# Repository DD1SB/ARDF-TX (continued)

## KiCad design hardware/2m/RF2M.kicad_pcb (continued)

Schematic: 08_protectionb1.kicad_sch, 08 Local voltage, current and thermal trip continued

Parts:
C104, C804: 1n; C_0603_1608Metric_E3; MPN CC0603JRNPO9BN102
C801, C802, C803: 100n; C_0603_1608Metric_E3; MPN CC0603KRX7R8BB104
D801, D802: BAT54 fault AND; D_SOD-323_E3; MPN BAT54WS-7-F
R117: 1k; R_0603_1608Metric_E3; MPN RC0603FR-071KL
R118: 100k; R_0603_1608Metric_E3; MPN RC0603FR-07100KL; not fitted
R828: 5.11k; R_0603_1608Metric_E3; MPN RT0603BRD075K11L
R829: 4.02k; R_0603_1608Metric_E3; MPN RC0603FR-074K02L
R832, R833: 10k; R_0603_1608Metric_E3; MPN RC0603FR-0710KL
TP801: ISENSE; TestPoint_Pad_D1.0mm_E3; MPN PCB feature
TP802: POWER_FAULT_N; TestPoint_Pad_D1.0mm_E3; MPN PCB feature
U802, U803: LM339BDR; SOIC-14_3.9x8.7mm_P1.27mm_E3; MPN LM339BDR

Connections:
DRV_OV_REF: U802.9 (+); also elsewhere on the board
DRV_S: U802.8 (-); also elsewhere on the board
GND: C104.2, C801.2, C802.2, C803.2, C804.2, R118.2, R829.2, U802.12 (V-), U803.12 (V-); also elsewhere on the board
HARD_OK_N: D802.1 (K), R833.1, U802.13, U802.14, U803.1, U803.2, U803.13, U803.14; also elsewhere on the board
ISENSE: R828.1, TP801.1; also elsewhere on the board
ISENSE_F: C804.1, R828.2, R829.1, U803.4 (-)
OV_REF: U802.7 (+); also elsewhere on the board
PACK_OK_N: D801.1 (K), R832.1, U802.1, U802.2; also elsewhere on the board
PA_RAIL_ADC: C104.1, R117.2, R118.1; also elsewhere on the board
POWER_FAULT_N: D801.2 (A), D802.2 (A), TP802.1; also elsewhere on the board
REG_OV_REF: U802.11 (+); also elsewhere on the board
TEMP_HIGH: U803.11 (+); also elsewhere on the board
TEMP_LOW: U803.6 (-); also elsewhere on the board
TEMP_S: U803.7 (+), U803.10 (-); also elsewhere on the board
UV_REF: U802.4 (-); also elsewhere on the board
V3V3: C801.1, C802.1, C803.1, R832.2, R833.2, U802.3 (V+), U803.3 (V+); also elsewhere on the board
VBAT_S: U802.5 (+), U802.6 (-); also elsewhere on the board
VPA_OV_REF: U803.9 (+); also elsewhere on the board
VPA_S: U803.8 (-); also elsewhere on the board
VREF1V0: U803.5 (+); also elsewhere on the board
VREG_S: R117.1, U802.10 (-); also elsewhere on the board

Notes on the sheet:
08 Local voltage, current and thermal trip continued
M5B-E6R2 / integrated evaluation PCB / NOT RELEASED / hardware tests NOT_RUN
M5B-E6R2: REVIEW / ALL hardware measurements NOT RUN / no ordering or manufacture.

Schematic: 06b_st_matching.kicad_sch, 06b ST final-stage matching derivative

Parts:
C631, C633: 22p; C_0603_1608Metric_E3; MPN GRM1885C1H220JA01D
C632, C634, C639: 330p; C_0603_1608Metric_E3; MPN GRM1885C1H331JA01D
C635: 1u; C_0603_1608Metric_E3; MPN GRM188R71E105KA12D
C636: 33p; C_0603_1608Metric_E3; MPN GRM1885C1H330JA01D
C637: 100p; C_0603_1608Metric_E3; MPN GRM1885C1H101JA01D
C638: 39p; C_0603_1608Metric_E3; MPN GRM1885C1H390JA01D
L634: 47n; Coilcraft_0603HC_Doc218; MPN 0603HC-47NXJRW
L635: 33n; Coilcraft_1812SMS_Doc184; MPN 1812SMS-33NJLC
L638: 18.5n; Coilcraft_A05T_Doc107; MPN A05TJLC
TL603: 50R 6.1129mm; TL50_E3_6p1129mm; MPN PCB microstrip feature
TL604: 50R 6.4956mm; TL50_E3_6p4956mm; MPN PCB microstrip feature
TL605: 50R 5.691mm; TL50_E3_5p691mm; MPN PCB microstrip feature
TL606: 50R 2.1587mm; TL50_E3_2p1587mm; MPN PCB microstrip feature
TL607: 50R 10.7933mm; TL50_E3_10p7933mm; MPN PCB microstrip feature
TL608: 50R 12.167mm; TL50_E3_12p167mm; MPN PCB microstrip feature
TL609: 50R 1.9624mm; TL50_E3_1p9624mm; MPN PCB microstrip feature

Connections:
GND: C631.2, C633.2, C634.2, C635.2, C636.2, C637.2, C638.2; also elsewhere on the board
MMIC_AC: TL603.1 (IN); also elsewhere on the board
PA_DRAIN: L635.2, TL606.1 (IN); also elsewhere on the board
PA_GATE: TL605.2 (OUT); also elsewhere on the board
ST_DC_BLOCK: C639.2, TL609.1 (IN)
ST_IS_A: C631.1, C632.1, TL603.2 (OUT)
ST_IS_B: C632.2, TL604.1 (IN)
ST_IS_C: C633.1, L634.1, TL604.2 (OUT)
ST_IS_D: L634.2, TL605.1 (IN)
ST_LPF_IN: TL609.2 (OUT); also elsewhere on the board
ST_O_A: C636.1, TL606.2 (OUT), TL607.1 (IN)
ST_O_B: C637.1, L638.1, TL607.2 (OUT)
ST_O_C: C638.1, L638.2, TL608.1 (IN)
ST_O_D: C639.1, TL608.2 (OUT)
VMOD: C635.1; also elsewhere on the board
VPA: C634.1, L635.1; also elsewhere on the board

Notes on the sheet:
06b ST final-stage matching derivative
ST DocID17343 Rev1 Figs16/17/14. Traced topology; changed MMIC drive and supplyAM remain UNQUALIFIED. TLine symbols are PCB microstrip lengths, NOT purchased components or zero-length wire. No hardware measurements exist.
Input matching: original interstage source was PD84001 drain, not a50ohm MMIC. No claim of unchanged match or sufficient gain. Output matching/LPF retained. L63533n drain feed is a disclosed substitution for the contradictory35.5n/22n ST BOM entry. Use one integrated end-to-end commissioning proced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
M5B-E6R2: REVIEW / ALL hardware measurements NOT RUN / no ordering or manufacture.

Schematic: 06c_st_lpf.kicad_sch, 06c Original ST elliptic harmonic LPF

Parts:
C641: 3.3p; C_0603_1608Metric_E3; MPN GRM1885C1H3R3CA01D
C642: 18p; C_0603_1608Metric_E3; MPN GRM1885C1H180JA01D
C643: 12p; C_0603_1608Metric_E3; MPN GRM1885C1H120JA01D
C644, C646: 22p; C_0603_1608Metric_E3; MPN GRM1885C1H220JA01D
C645: 27p; C_0603_1608Metric_E3; MPN GRM1885C1H270JA01D
C647: 15p; C_0603_1608Metric_E3; MPN GRM1885C1H150JA01D
L641: 39n; Coilcraft_1008CS_Doc101; MPN 1008CS-390XJLC
L642: 22n; Coilcraft_1008CS_Doc101; MPN 1008CS-220XJLC
L643: 27n; Coilcraft_1008CS_Doc101; MPN 1008CS-270XJLC

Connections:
GND: C644.2, C645.2, C646.2, C647.2; also elsewhere on the board
NORMAL_RF: C643.2, C647.1, L643.2; also elsewhere on the board
ST_F1: C641.2, C642.1, C645.1, L641.2, L642.1
ST_F2: C642.2, C643.1, C646.1, L642.2, L643.1
ST_LPF_IN: C641.1, C644.1, L641.1; also elsewhere on the board

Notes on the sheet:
06c Original ST elliptic harmonic LPF
ST DocID17343 Rev1 Figs16/17/14. Traced topology; changed MMIC drive and supplyAM remain UNQUALIFIED. TLine symbols are PCB microstrip lengths, NOT purchased components or zero-length wire. No hardware measurements exist.
Input matching: original interstage source was PD84001 drain, not a50ohm MMIC. No claim of unchanged match or sufficient gain. Output matching/LPF retained. L63533n drain feed is a disclosed substitution for the contradictory35.5n/22n ST BOM entry. Use one integrated end-to-end commissioning proced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
M5B-E6R2: REVIEW / ALL hardware measurements NOT RUN / no ordering or manufacture.

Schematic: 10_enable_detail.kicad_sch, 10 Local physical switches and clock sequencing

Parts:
C931, C940, C941: 100n; C_0603_1608Metric_E3; MPN CC0603KRX7R8BB104
D930: BAT54WS; D_SOD-323_E3; MPN BAT54WS-7-F
R930: 10k; R_0603_1608Metric_E3; MPN RC0603FR-0710KL
R931: 330; R_0603_1608Metric_E3; MPN RC0603FR-07330RL
R932, R940: 100k; R_0603_1608Metric_E3; MPN RC0603FR-07100KL
TP940: Captured profile; TestPoint_Pad_D1.0mm_E3; MPN PCB feature
U205: 74HC21D,653; SOIC-14_3.9x8.7mm_P1.27mm_E3; MPN 74HC21D,653
U206: 74HC11D,653; SOIC-14_3.9x8.7mm_P1.27mm_E3; MPN 74HC11D,653
U305: TPS22810DBVR; SOT-23-6_E3; MPN TPS22810DBVR
U601: SN74LVC1G125DBVR; SOT-23-5_E3; MPN SN74LVC1G125DBVR

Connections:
ARM: U205.5; also elsewhere on the board
ARM_DELAY: U205.2; also elsewhere on the board
CLEAR_A: U205.9, U206.5, U206.13; also elsewhere on the board
CLK_NORMAL: U601.2 (A); also elsewhere on the board
CLOCK_OFF: U601.1 (OE_N); also elsewhere on the board
CLR_N: U205.8; also elsewhere on the board
CONV_EN: U206.8; also elsewhere on the board
DRIVER_ON: U305.3 (EN); also elsewhere on the board
GND: C931.2, C940.2, C941.2, R932.2, R940.2, U205.7 (GND), U206.7 (GND), U305.2 (GND), U601.3 (GND); also elsewhere on the board
NORMAL_CLOCK_BUF: U601.4 (Y); also elsewhere on the board
NORMAL_FAST_OFF: D930.1 (K), R931.1
NORMAL_PERMIT: R930.1, R931.2, R940.1, U206.12; also elsewhere on the board
NORMAL_Q: U206.2; also elsewhere on the board
NORMAL_RC: C931.1, D930.2 (A), R930.2, R932.1; also elsewhere on the board
PATH_Q: U206.4; also elsewhere on the board
PA_PREPARE: U206.9; also elsewhere on the board
PROFILE_Q: TP940.1; also elsewhere on the board
RUN_HEALTH: U205.10; also elsewhere on the board
SLOT: U205.4; also elsewhere on the board
SRC_ON: U206.10; also elsewhere on the board
TRAIN_PERMIT: U206.6; also elsewhere on the board
TX_OK: U205.6, U206.1, U206.3
V3V3: C941.1, U205.12, U205.13, U205.14 (VCC), U206.11, U206.14 (VCC), U601.5 (VCC); also elsewhere on the board
VALID_ARM: U205.1; also elsewhere on the board
VDRV_FILTER: C940.1, U305.1 (VIN); also elsewhere on the board
VDRV_RF: U305.5 (QOD), U305.6 (VOUT); also elsewhere on the board

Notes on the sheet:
10 Local physical switches and clock sequencing
M5B-E6R2 / integrated evaluation PCB / NOT RELEASED / hardware tests NOT_RUN
M5B-E6R2: REVIEW / ALL hardware measurements NOT RUN / no ordering or manufacture.

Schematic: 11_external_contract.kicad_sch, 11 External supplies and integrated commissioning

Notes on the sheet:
11 External supplies and integrated commissioning
M5B-E6R2 / integrated evaluation PCB / NOT RELEASED / hardware tests NOT_RUN
M5B-E6R2: REVIEW / ALL hardware measurements NOT RUN / no ordering or manufacture.

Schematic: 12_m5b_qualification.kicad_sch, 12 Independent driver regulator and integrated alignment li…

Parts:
C950, C951: 4.7u; C_0805_2012Metric_E3; MPN GRM21BR71E475KA73L
C960: 22u; C_1210_3225Metric_E3; MPN GRM32ER71V226KE15L
C961: 22u; C_1210_3225Metric_E3; MPN GRM32ER71V226KE15L; not fitted
R650: 0; R_0603_1608Metric_E3; MPN RC0603JR-070RL
R651: 49.9; R_1206_3216Metric_E3; MPN RC1206FR-0749R9L; not fitted
R950: 58.2k; R_0603_1608Metric_E3; MPN RT0603BRD0758K2L
R951: 10k; R_0603_1608Metric_E3; MPN RT0603BRD0710KL
R952: 0; R_1206_3216Metric_E3; MPN RC1206JR-070RL
TP950: DRV pre5.456V; TestPoint_Pad_D1.0mm_E3; MPN PCB feature
TP951: MMIC isolated5V; TestPoint_Pad_D1.0mm_E3; MPN PCB feature
U950: TLV76701DRVR; WSON-6-1EP_2x2mm_P0.65mm_EP1x1.6mm_E3; MPN TLV76701DRVR

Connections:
CONV_EN: U950.4 (EN); also elsewhere on the board
DRV_PRE_FB: R950.2, R951.1, U950.2 (FB)
GND: C950.2, C951.2, C960.2, C961.2, R651.2, R951.2, U950.3 (GND), U950.5 (GND), U950.7 (EP_GND); also elsewhere on the board
MMIC_AC: R650.2; also elsewhere on the board
MMIC_COUPLED: R650.1, R651.1; also elsewhere on the board
VDRV_LDO_IN: C950.1, U950.6 (IN); also elsewhere on the board
VDRV_MMIC: R952.2, TP951.1; also elsewhere on the board
VDRV_PREREG: C951.1, R950.1, TP950.1, U950.1 (OUT); also elsewhere on the board
VDRV_RF: R952.1; also elsewhere on the board
VIN_CONV: C960.1, C961.1; also elsewhere on the board

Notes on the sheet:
12 Independent driver regulator and integrated alignment links
Pre-regulation5.456V then existing5V LDO. Rated18V switch. No20us RC assumption is claimed as protection proof. Fit driver link only after power-only qualification. RF link and optional50ohm load permit alignment on THIS board.
M5B-E6R2: REVIEW / ALL hardware measurements NOT RUN / no ordering or manufacture.

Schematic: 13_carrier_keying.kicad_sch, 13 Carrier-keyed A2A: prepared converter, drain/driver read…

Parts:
C970, C971, C972, C973: 100n; C_0603_1608Metric_E3; MPN GRM188R71H104KA93D
R970: 0.05; R_2512_6332Metric_E3; MPN WSL2512R0500FEA
R971, R975, R979, R980, R981, R982, R983, R984, R986: 100k; R_0603_1608Metric_E3; MPN RT0603BRD07100KL
R972, R976: 33k; R_0603_1608Metric_E3; MPN RT0603BRD0733KL
R973: 330k; R_0603_1608Metric_E3; MPN RT0603BRD07330KL
R974: 2.49k; R_0603_1608Metric_E3; MPN RT0603BRD072K49L
R977: 19.1k; R_0603_1608Metric_E3; MPN RT0603BRD0719K1L
R978, R985: 10k; R_0603_1608Metric_E3; MPN RT0603BRD0710KL
TP970: Pass collector before current shunt; TestPoint_Pad_D1.0mm_E3; MPN PCB feature
TP971: Regulated current shunt upstream; TestPoint_Pad_D1.0mm_E3; MPN PCB feature
TP972: RF inhibit; TestPoint_Pad_D1.0mm_E3; MPN PCB feature
TP973: MMIC enable; TestPoint_Pad_D1.0mm_E3; MPN PCB feature
TP974: Modulator clamp; TestPoint_Pad_D1.0mm_E3; MPN PCB feature
TP975: PA readiness; TestPoint_Pad_D1.0mm_E3; MPN PCB feature
TP976: Driver readiness; TestPoint_Pad_D1.0mm_E3; MPN PCB feature
U970: TLV7032DGKR; TLV7032_DGK_E6R2; MPN TLV7032DGKR
U971: SN74LVC1G00DBVR; LVC1G00_DBV_E6R2; MPN SN74LVC1G00DBVR
U972: SN74LVC2G32DCTR; LVC2G32_DCT_E6R2; MPN SN74LVC2G32DCTR
U973: SN74LVC1G04DBVR; LVC1G04_DBV_E6R2; MPN SN74LVC1G04DBVR

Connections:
CLOCK_OFF: R981.1, TP972.1, U972.3 (2Y); also elsewhere on the board
DRIVER_ON: R982.1, TP973.1, U973.4 (Y); also elsewhere on the board
DRV_READY: R980.1, TP976.1, U970.7 (OUTB), U971.2 (B)
DRV_READY_REF: R977.2, R978.1, U970.6 (INB-)
DRV_READY_S: R975.2, R976.1, U970.5 (INB+)
GND: C970.2, C971.2, C972.2, C973.2, R972.2, R974.2, R976.2, R978.2, R979.2, R980.2, R982.2, R986.2, U970.4 (GND), U971.3 (GND), U972.4 (GND), U973.3 (GND); also elsewhere on the board
KEY_N: U972.2 (1B); also elsewhere on the board
LOCAL_MOD_OFF: R984.1, TP974.1, U972.5 (2A), U972.7 (1Y), U973.2 (A); also elsewhere on the board
MOD_COMMAND_OFF_BASE: R985.2, R986.1; also elsewhere on the board
NORMAL_OFF: R985.1, U972.1 (1A); also elsewhere on the board
RF_NOT_READY: R983.1, U971.4 (Y), U972.6 (2B)
V3V3: C970.1, C971.1, C972.1, C973.1, R973.1, R977.1, R981.2, R983.2, R984.2, U970.8 (VCC), U971.5 (VCC), U972.8 (VCC), U973.5 (VCC); also elsewhere on the board
VDRV_MMIC: R975.1; also elsewhere on the board
VPA: R970.2, R971.1; also elsewhere on the board
VPA_PRE: R970.1, TP970.1; also elsewhere on the board
VPA_READY: R979.1, TP975.1, U970.1 (OUTA), U971.1 (A)
VPA_READY_REF: R973.2, R974.1, U970.2 (INA-)
VPA_READY_S: R971.2, R972.1, U970.3 (INA+)
VREG_SWITCH: TP971.1; also elsewhere on the board

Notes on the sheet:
13 Carrier-keyed A2A: prepared converter, drain/driver readiness and probes
Architecture C: LOCAL_MOD_OFF=NORMAL_OFF OR KEY_N; DRIVER_ON=NOT LOCAL_MOD_OFF. CLOCK_OFF=LOCAL_MOD_OFF OR NOT(VPA_READY AND DRV_READY). Native safety delay/fastkill remain in series. AF_PWM must provide shaped sine envelope; KEY gives preparation lead. No converter re-start per Morse element. Exis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
M5B-E6R2: REVIEW / ALL hardware measurements NOT RUN / no ordering or manufacture.
Carrier keying

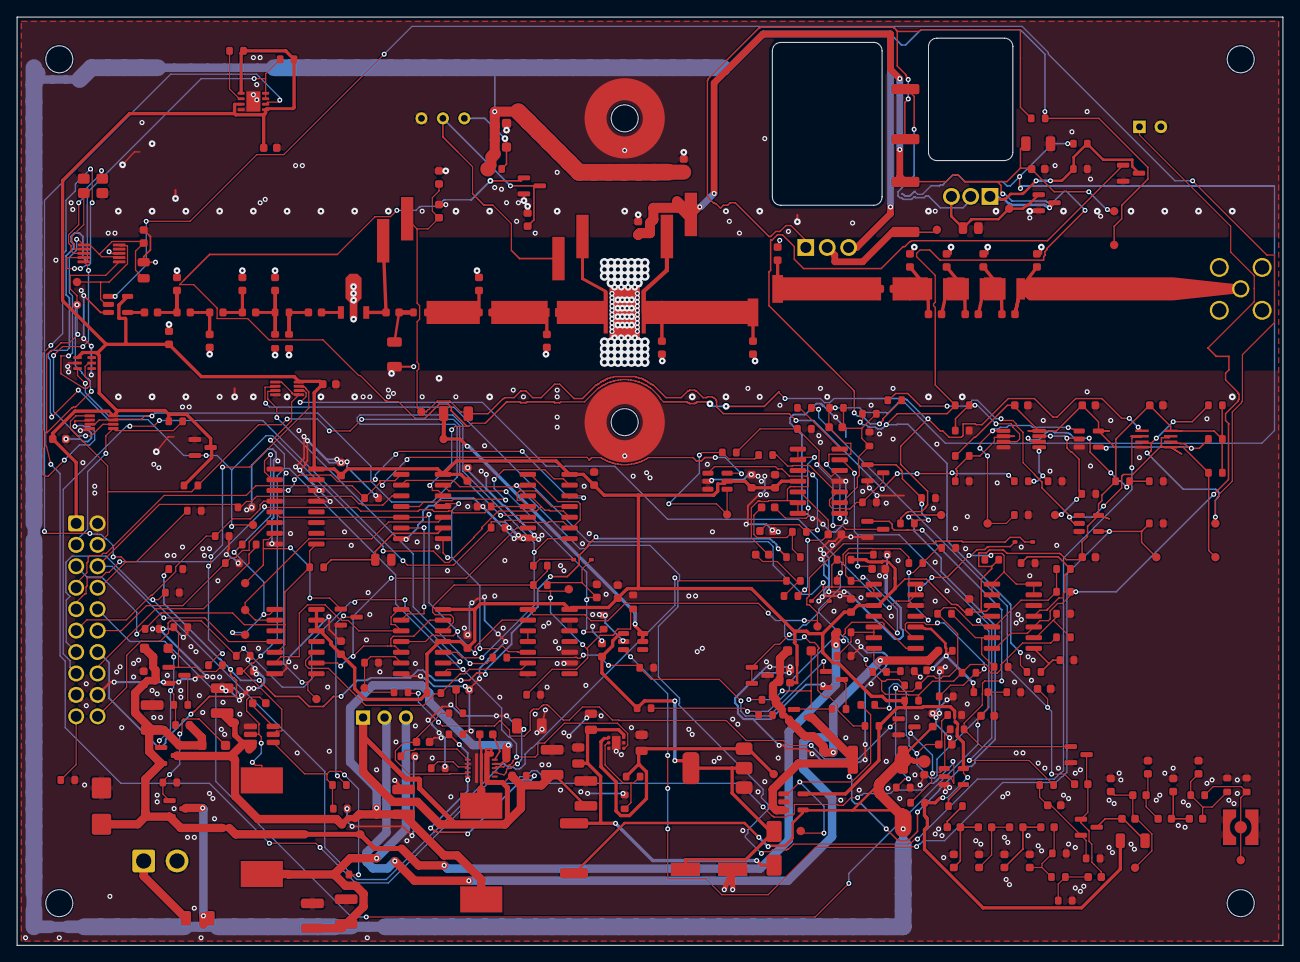
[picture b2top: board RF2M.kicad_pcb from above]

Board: 2 copper layers, 150.0 x 110.0 mm, 358 parts (0 on the bottom side), 181 nets.

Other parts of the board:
H1, H2, H3, H4, H5, H6: MountingHole_3.2mm_M3; MountingHole_3.2mm_M3_E3

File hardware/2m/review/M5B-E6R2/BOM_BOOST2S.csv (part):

variant,fleet,ref,value,MPN,footprint,quantity_board,order_pooled,MOQ,multiple,unit_net_EUR,allocated_net_EUR,evidence,supplier,availability,source
BOOST2S,7,J101,Controller 20 pin,61202021621,ARDF_2M:WR_BHD_61202021621,1,7,1,1,0.65,0.65,ESTIMATE,Wurth authorized distributor,Not independently basket-confirmed,https://www.we-online.com/components/products/datasheet/6120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
BOOST2S,7,R101,18.2k,RC0603FR-0718K2L,ARDF_2M:R_0603_1608Metric_E3,1,7,1,1,0.02,0.02,ESTIMATE,OPEN,Not independently basket-confirmed,https://www.yageo.com/en/ProductCategory/Resistors
BOOST2S,7,R102,4.7k,RC0603FR-074K7L,ARDF_2M:R_0603_1608Metric_E3,1,56,1,1,0.02,0.02,ESTIMATE,OPEN,Not independently basket-confirmed,https://www.yageo.com/en/ProductCategory/Resistors
BOOST2S,7,R103,4.7k,RC0603FR-074K7L,ARDF_2M:R_0603_1608Metric_E3,1,56,1,1,0.02,0.02,ESTIMATE,OPEN,Not independently basket-confirmed,https://www.yageo.com/en/ProductCategory/Resistors
BOOST2S,7,R104,100k,RC0603FR-07100KL,ARDF_2M:R_0603_1608Metric_E3,1,140,1,1,0.02,0.02,ESTIMATE,OPEN,Not independently basket-confirmed,https://www.yageo.com/en/ProductCategory/Resistors
BOOST2S,7,R105,100k,RC0603FR-07100KL,ARDF_2M:R_0603_1608Metric_E3,1,140,1,1,0.02,0.02,ESTIMATE,OPEN,Not independently basket-confirmed,https://www.yageo.com/en/ProductCategory/Resistors
BOOST2S,7,R106,100k,RC0603FR-07100KL,ARDF_2M:R_0603_1608Metric_E3,1,140,1,1,0.02,0.02,ESTIMATE,OPEN,Not independently basket-confirmed,https://www.yageo.com/en/ProductCategory/Resistors
BOOST2S,7,R107,100k,RC0603FR-07100KL,ARDF_2M:R_0603_1608Metric_E3,1,140,1,1,0.02,0.02,ESTIMATE,OPEN,Not independently basket-confirmed,https://www.yageo.com/en/ProductCategory/Resistors
BOOST2S,7,R108,100k,RC0603FR-07100KL,ARDF_2M:R_0603_1608Metric_E3,1,140,1,1,0.02,0.02,ESTIMATE,OPEN,Not independently basket-confirmed,https://www.yageo.com/en/ProductCategory/Resistors
BOOST2S,7,R109,100k,RC0603FR-07100KL,ARDF_2M:R_0603_1608Metric_E3,1,140,1,1,0.02,0.02,ESTIMATE,OPEN,Not independently basket-confirmed,https://www.yageo.com/en/ProductCategory/Resistors
BOOST2S,7,R110,100k,RC0603FR-07100KL,ARDF_2M:R_0603_1608Metric_E3,1,140,1,1,0.02,0.02,ESTIMATE,OPEN,Not independently basket-confirmed,https://www.yageo.com/en/ProductCategory/Resistors
BOOST2S,7,R111,100k,RC0603FR-07100KL,ARDF_2M:R_0603_1608Metric_E3,1,140,1,1,0.02,0.02,ESTIMATE,OPEN,Not independently basket-confirmed,https://www.yageo.com/en/ProductCategory/Resistors
BOOST2S,7,R112,100k,RC0603FR-07100KL,ARDF_2M:R_0603_1608Metric_E3,1,140,1,1,0.02,0.02,ESTIMATE,OPEN,Not independently basket-confirmed,https://www.yageo.com/en/ProductCategory/Resistors
BOOST2S,7,R115,100k,RC0603FR-07100KL,ARDF_2M:R_0603_1608Metric_E3,1,140,1,1,0.02,0.02,ESTIMATE,OPEN,Not independently basket-confirmed,https://www.yageo.com/en/ProductCategory/Resistors
BOOST2S,7,R116,100k,RC0603FR-07100KL,ARDF_2M:R_0603_1608Metric_E3,1,140,1,1,0.02,0.02,ESTIMATE,OPEN,Not independently basket-confirmed,https://www.yageo.com/en/ProductCategory/Resistors
BOOST2S,7,U101,TPS22919DCKR,TPS22919DCKR,ARDF_2M:SOT-363_SC-70-6_E3,1,7,1,1,0.25,0.25,ESTIMATE,OPEN,Not independently basket-confirmed,https://www.ti.com/lit/ds/symlink/tps22919.pdf
BOOST2S,7,U102,SN74LVC2G66DCUR,SN74LVC2G66DCUR,ARDF_2M:VSSOP-8_2.3x2mm_P0.5mm_E3,1,7,1,1,0.33,0.33,ESTIMATE,OPEN,Not independently basket-confirmed,https://www.ti.com/lit/ds/symlink/sn74lvc2g66.pdf
BOOST2S,7,U103,Si5351A-B-GT,Si5351A-B-GT,ARDF_2M:MSOP-10_3x3mm_P0.5mm_E3,1,7,1,1,1.35,1.35,ESTIMATE,OPEN,Not independently basket-confirmed,https://www.skyworksinc.com/-/media/SkyWorks/SL/documents/pu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
BOOST2S,7,Y101,25MHz CL10p 10/10ppm,ABM8-25.000MHZ-10-B1U-T,ARDF_2M:Crystal_SMD_3225-4Pin_3.2x2.5mm_E3,1,7,1,1,0.35,0.35,ESTIMATE,OPEN,Not independently basket-confirmed,
BOOST2S,7,C101,100n,CC0603KRX7R8BB104,ARDF_2M:C_0603_1608Metric_E3,1,175,1,1,0.045,0.045,ESTIMATE,OPEN,Not independently basket-confirmed,
BOOST2S,7,C102,100n,CC0603KRX7R8BB104,ARDF_2M:C_0603_1608Metric_E3,1,175,1,1,0.045,0.045,ESTIMATE,OPEN,Not independently basket-confirmed,
BOOST2S,7,C103,1u,CC0805KKX7R9BB105,ARDF_2M:C_0805_2012Metric_E3,1,21,1,1,0.045,0.045,ESTIMATE,OPEN,Not independently basket-confirmed,
BOOST2S,7,U201,TPS3431SDRBR,TPS3431SDRBR,ARDF_2M:VSON-8-1EP_3x3mm_P0.65mm_EP1.65x2.4mm_E3,1,7,1,1,0.85,0.85,ESTIMATE,OPEN,Not independently basket-confirmed,https://www.ti.com/lit/ds/symlink/tps3431.pdf
BOOST2S,7,R201,10k,RC0603FR-0710KL,ARDF_2M:R_0603_1608Metric_E3,1,196,1,1,0.02,0.02,ESTIMATE,OPEN,Not independently basket-confirmed,https://www.yageo.com/en/ProductCategory/Resistors
BOOST2S,7,R202,10k,RC0603FR-0710KL,ARDF_2M:R_0603_1608Metric_E3,1,196,1,1,0.02,0.02,ESTIMATE,OPEN,Not independently basket-confirmed,https://www.yageo.com/en/ProductCategory/Resistors
BOOST2S,7,C201,100n,CC0603KRX7R8BB104,ARDF_2M:C_0603_1608Metric_E3,1,175,1,1,0.045,0.045,ESTIMATE,OPEN,Not independently basket-confirmed,
BOOST2S,7,U208,TLV803EA29DBZR,TLV803EA29DBZR,ARDF_2M:SOT-23_E3,1,7,1,1,0.19,0.19,ESTIMATE,OPEN,Not independently basket-confirmed,https://www.ti.com/lit/ds/symlink/tlv803e.pdf
BOOST2S,7,U202,"74HC174D,653","74HC174D,653",ARDF_2M:SOIC-16_3.9x9.9mm_P1.27mm_E3,1,7,1,1,0.48,0.48,ESTIMATE,OPEN,Not independently basket-confirmed,https://assets.nexperia.com/documents/data-sheet/74HC_HCT174.pdf
BOOST2S,7,U203,"74HC14D,653","74HC14D,653",ARDF_2M:SOIC-14_3.9x8.7mm_P1.27mm_E3,1,7,1,1,0.28,0.28,ESTIMATE,OPEN,Not independently basket-confirmed,https://assets.nexperia.com/documents/data-sheet/74HC_HCT14.pdf
BOOST2S,7,U204,"74HC11D,653","74HC11D,653",ARDF_2M:SOIC-14_3.9x8.7mm_P1.27mm_E3,1,14,1,1,0.28,0.28,ESTIMATE,OPEN,Not independently basket-confirmed,https://assets.nexperia.com/documents/data-sheet/74HC_HCT11.pdf
BOOST2S,7,U207,"74HC32D,653","74HC32D,653",ARDF_2M:SOIC-14_3.9x8.7mm_P1.27mm_E3,1,7,1,1,0.28,0.28,ESTIMATE,OPEN,Not independently basket-confirmed,https://assets.nexperia.com/documents/data-sheet/74HC_HCT32.pdf
BOOST2S,7,R203,10k,RC0603FR-0710KL,ARDF_2M:R_0603_1608Metric_E3,1,196,1,1,0.02,0.02,ESTIMATE,OPEN,Not independently basket-confirmed,https://www.yageo.com/en/ProductCategory/Resistors
BOOST2S,7,C202,1u,CC0805KKX7R9BB105,ARDF_2M:C_0805_2012Metric_E3,1,21,1,1,0.045,0.045,ESTIMATE,OPEN,Not independently basket-confirmed,
BOOST2S,7,R204,100k,RC0603FR-07100KL,ARDF_2M:R_0603_1608Metric_E3,1,140,1,1,0.02,0.02,ESTIMATE,OPEN,Not independently basket-confirmed,https://www.yageo.com/en/ProductCategory/Resistors
BOOST2S,7,R205,100k,RC0603FR-07100KL,ARDF_2M:R_0603_1608Metric_E3,1,140,1,1,0.02,0.02,ESTIMATE,OPEN,Not independently basket-confirmed,https://www.yageo.com/en/ProductCategory/Resistors
BOOST2S,7,C203,100n,CC0603KRX7R8BB104,ARDF_2M:C_0603_1608Metric_E3,1,175,1,1,0.045,0.045,ESTIMATE,OPEN,Not independently basket-confirmed,
BOOST2S,7,C204,100n,CC0603KRX7R8BB104,ARDF_2M:C_0603_1608Metric_E3,1,175,1,1,0.045,0.045,ESTIMATE,OPEN,Not independently basket-confirmed,
BOOST2S,7,C205,100n,CC0603KRX7R8BB104,ARDF_2M:C_0603_1608Metric_E3,1,175,1,1,0.045,0.045,ESTIMATE,OPEN,Not independently basket-confirmed,
BOOST2S,7,C206,100n,CC0603KRX7R8BB104,ARDF_2M:C_0603_1608Metric_E3,1,175,1,1,0.045,0.045,ESTIMATE,OPEN,Not independently basket-confirmed,
BOOST2S,7,C207,100n,CC0603KRX7R8BB104,ARDF_2M:C_0603_1608Metric_E3,1,175,1,1,0.045,0.045,ESTIMATE,OPEN,Not independently basket-confirmed,
BOOST2S,7,C208,100n,CC0603KRX7R8BB104,ARDF_2M:C_0603_1608Metric_E3,1,175,1,1,0.045,0.045,ESTIMATE,OPEN,Not independently basket-confirmed,
BOOST2S,7,R206,1k,RC0603FR-071KL,ARDF_2M:R_0603_1608Metric_E3,1,70,1,1,0.02,0.02,ESTIMATE,OPEN,Not independently basket-confirmed,https://www.yageo.com/en/ProductCategory/Resistors
BOOST2S,7,J301,Protected pack JST VH,B2P-VH(LF)(SN),ARDF_2M:JST_VH_B2P-VH_1x02_P3.96mm_Vertical_E3,1,7,1,1,0.35,0.35,ESTIMATE,JST authorized distributor,Not independently basket-confirmed,https://www.jst.com/wp-content/uploads/2025/06/eVH.pdf
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
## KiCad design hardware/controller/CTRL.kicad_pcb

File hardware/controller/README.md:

# ARDF-TX universal controller — M6-L2 candidate

Active KiCad 10 sources are CTRL.kicad_pro, CTRL.kicad_sch, its referenced sheets and CTRL.kicad_pcb, with local ARDF_CTL libraries. M6-L2 selects ESP32-S3-WROOM-1U-N4 (4 MB flash, no PSRAM), adds optional FoxPro2 compatibility and an optional TCA9534APWR eight-line GPIO interface. See the [review package](review/M6-L2/README.md), [decision](../../docs/M6_L2_REVIEW_DECISION.md) and [reproduction commands](review/M6-L2/REPRODUCE.md).

[M6-L1](review/M6-L1/README.md) remains the previous independently reviewed baseline. Its NO_LORA, LORA_433 and LORA_868 options, module footprint and RF feed remain. RF80/RF2M sources and historical review packages are immutable. All existing GPIO functions, protected battery ID, USB/reset/RTC facilities, RF branch isolation, static controls and fail-off architecture are retained. PACK_ID_FRONTEND_REV2 calibration and the external 10k/22k identities remain mandatory.

The default build retains recovery UART routing and omits both new interfaces. FoxPro population replaces the recovery links with physically separate routing links; never fit both sets. The ESP32's 2.4 GHz antenna is separate from LoRa. Legacy FoxPro battery display is unavailable on both 2S and 4S. GPIO3/46 service links remain open; GPIO45 remains NC without breakout. Select one of the 48 explicit RF/LoRa/interface populations and use its assembly/placement files. An SX1262 response cannot identify its RF band; unknown LoRa disables LoRa TX while otherwise valid autonomous operation remains available.

Independent review and [fresh final reproduction](../../docs/M6_L2_FINAL_REPRODUCTION.md) support GO for five controlled bare evaluation boards. The verified revision is authorized for normal GitHub publication. All physical ESP32/USB/recovery, genuine FoxPro, antenna/coexistence, accessory, fault, power-sequencing and RF/thermal qualification is NOT_RUN. Host foundations are not complete contest firmware. No supplier upload, order, purchase, hardware energizing, acceptance tag or production release is authorized.

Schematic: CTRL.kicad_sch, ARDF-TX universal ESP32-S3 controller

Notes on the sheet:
M6-L1 UNIVERSAL CONTROLLER / ENGINEERING CANDIDATE ESP32-S3-WROOM-1-N4 / RV-3032-C7 / isolated RF80 + RF2M contracts No manufacturing or operational release. All physical tests NOT_RUN. LoRa optional433/868 nominal package/RF-feed audit M6-L1; trusted assembly configuration required. Physical tests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

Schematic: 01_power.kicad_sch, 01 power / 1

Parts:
C1, C6: 100n; C_0603_1608Metric_CTL; MPN CL10B104KB8NNNC
C2, C3: 4.7u 50V; C_1210_3225Metric_CTL; MPN GRM32ER71H475KA88L
C4, C5: 22u 10V; C_1206_3216Metric_CTL; MPN CL31A226KPHNNNE
D1: 100V 2A reverse block; D_SMA_CTL; MPN STPS2H100A
D2: 18V unidirectional TVS; D_SMB_CTL; MPN SMBJ18A
D3: USB low-drop OR; D_SMA_CTL; MPN STPS1L30A
D4: Low leakage battery OR; D_SMA_CTL; MPN S1M-E3/61T
D21: USB reverse-leak clamp 5.1V; D_SOD-123F_CTL; MPN BZT52H-B5V1,115
F1: 1A 63V fast; Fuse_Bourns_SF1206F; MPN SF-1206F100-2
J1: PACK / GND / ID; JST_XH_B3B_Standard; MPN B3B-XH-A(LF)(SN)
L1: 4.7uH 4.6Arms; L_Bourns_SRP5030T_CTL; MPN SRP5030T-4R7M
R1: 470k; R_0603_1608Metric_CTL; MPN RC0603FR-07470KL
R2: 47k; R_0603_1608Metric_CTL; MPN RC0603FR-0747KL
R3: 27k; R_0603_1608Metric_CTL; MPN RC0603FR-0727KL
U1: AP63203WU-7; TSOT-23-6_CTL; MPN AP63203WU-7

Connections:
BAT_DIV: R1.2, R2.1; also elsewhere on the board
BUCK_BST: C1.1, U1.6 (6_BST)
BUCK_SW: C1.2, L1.1, U1.5 (5_SW)
GND: C2.2, C3.2, C4.2, C5.2, C6.2, D2.2 (A), D21.2 (A), J1.2 (2_IO), R2.2, U1.4 (4_GND); also elsewhere on the board
PACK_FUSED: D1.2 (A), F1.2
PACK_ID_EXC: R3.1; also elsewhere on the board
PACK_ID_RAW: J1.3 (3_IO), R3.2; also elsewhere on the board
PACK_PROT: D1.1 (K), D2.1 (K), D4.2 (A), R1.1; also elsewhere on the board
PACK_RAW: F1.1, J1.1 (1_IO)
USB_LIMIT: D3.2 (A), D21.1 (K); also elsewhere on the board
V3V3: C4.1, C5.1, C6.1, L1.2, U1.1 (1_FB); also elsewhere on the board
VIN_SYS: C2.1, C3.1, D3.1 (K), D4.1 (K), U1.2 (2_EN), U1.3 (3_VIN); also elsewhere on the board

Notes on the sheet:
01 power / 1
M6-C1R1 candidate: REVIEW / ALL hardware measurements NOT RUN / no ordering or manufacture.

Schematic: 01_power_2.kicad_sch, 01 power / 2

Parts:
D22: BAS116 ID excitation isolation; SOT-23_CTL; MPN BAS116,235
D23: BAT54H negative ID clamp; D_SOD-123F_CTL; MPN BAT54H,115
Q1: MMBT3904; SOT-23_CTL; MPN MMBT3904LT1G
R4, R5, R19: 100k; R_0603_1608Metric_CTL; MPN RC0603FR-07100KL
R6, R7: 10k; R_0603_1608Metric_CTL; MPN RC0603FR-0710KL
R8: 180k; R_0603_1608Metric_CTL; MPN RC0603FR-07180KL
R9: 33k; R_0603_1608Metric_CTL; MPN RC0603FR-0733KL

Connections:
BATT_BASE: Q1.1 (1_B), R4.2, R5.1
GND: D23.2 (A), Q1.2 (2_E), R5.2, R7.2, R9.2, R19.2; also elsewhere on the board
PACK_ABSENT: Q1.3 (3_C), R6.2; also elsewhere on the board
PACK_ID_ADC: R19.1; also elsewhere on the board
PACK_ID_EXC: D22.3 (3_K); also elsewhere on the board
PACK_ID_RAW: R8.1; also elsewhere on the board
PACK_ID_SAFE: D23.1 (K), R8.2, R9.1; also elsewhere on the board
PACK_PROT: D22.1 (1_A), R4.1, R7.1; also elsewhere on the board
V3V3: R6.1; also elsewhere on the board

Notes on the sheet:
01 power / 2
M6-C1R1 candidate: REVIEW / ALL hardware measurements NOT RUN / no ordering or manufacture.

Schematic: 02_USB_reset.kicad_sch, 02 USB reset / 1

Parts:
C10: 100n; C_0603_1608Metric_CTL; MPN CL10B104KB8NNNC
C11: 4.7u 10V; C_0603_1608Metric_CTL; MPN CL10A475KP8NNNC
J2: USB-C native USB2; USB4105_Standard; MPN USB4105-GF-A
Q2: MMBT3904 VBUS sense; SOT-23_CTL; MPN MMBT3904LT1G
R10, R11: 5.1k; R_0603_1608Metric_CTL; MPN RC0603FR-075K1L
R12, R13, R64, R65: 100k; R_0603_1608Metric_CTL; MPN RC0603FR-07100KL
R14, R15: 22; R_0603_1608Metric_CTL; MPN RC0603FR-0722RL
R16, R63, R66: 10k; R_0603_1608Metric_CTL; MPN RC0603FR-0710KL
U2: TPS2553DBVR; SOT-23-6_CTL; MPN TPS2553DBVR
U3: USBLC6-2SC6; SOT-23-6_CTL; MPN USBLC6-2SC6
U4: TLV803EA30DBZR; SOT-23_CTL; MPN TLV803EA30DBZR

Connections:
GND: C10.2, C11.2, J2.A1 (A1_IO), J2.A12 (A12_IO), J2.B1 (B1_IO), J2.B12 (B12_IO), J2.SH (SH_IO), Q2.2 (2_E), R10.2, R11.2, R12.2, R63.2, R65.2, U2.2 (2_GND), U3.2 (2_IO), U4.1 (1_GND); also elsewhere on the board
MCU_EN: R16.2, U4.2 (2_RESET_N); also elsewhere on the board
USB_BASE: Q2.1 (1_B), R64.2, R65.1
USB_CC1: J2.A5 (A5_IO), R10.1
USB_CC2: J2.B5 (B5_IO), R11.1
USB_DM: R15.2; also elsewhere on the board
USB_DM_CONN: J2.A7 (A7_IO), J2.B7 (B7_IO), R15.1, U3.3 (3_IO), U3.4 (4_IO)
USB_DP: R14.2; also elsewhere on the board
USB_DP_CONN: J2.A6 (A6_IO), J2.B6 (B6_IO), R14.1, U3.1 (1_IO), U3.6 (6_IO)
USB_ILIM: R12.1, U2.5 (5_ILIM)
USB_LIMIT: U2.6 (6_OUT); also elsewhere on the board
USB_OC_N: R13.1, U2.4 (4_FAULT_N)
USB_VBUS: C11.1, J2.A4 (A4_IO), J2.A9 (A9_IO), J2.B4 (B4_IO), J2.B9 (B9_IO), R63.1, R64.1, U2.1 (1_IN), U2.3 (3_EN)
USB_VBUS_N: Q2.3 (3_C), R66.2; also elsewhere on the board
V3V3: C10.1, R13.2, R16.1, R66.1, U3.5 (5_IO), U4.3 (3_VDD); also elsewhere on the board

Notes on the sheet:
02 USB reset / 1
M6-C1R1 candidate: REVIEW / ALL hardware measurements NOT RUN / no ordering or manufacture.

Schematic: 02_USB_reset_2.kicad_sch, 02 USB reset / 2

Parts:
C12: 1u; C_0603_1608Metric_CTL; MPN CL10A105KB8NNNC
R17, R18: 10k; R_0603_1608Metric_CTL; MPN RC0603FR-0710KL
SW1: RESET; SW_SPST_TL3342_CTL; MPN TL3342F160QG
SW2: BOOT; SW_SPST_TL3342_CTL; MPN TL3342F160QG
SW3: START; SW_SPST_TL3342_CTL; MPN TL3342F160QG
SW4: STOP / hold reset; SW_SPST_TL3342_CTL; MPN TL3342F160QG

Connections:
BOOT: R17.2, SW2.1; also elsewhere on the board
GND: C12.2, SW1.2, SW2.2, SW3.2, SW4.2; also elsewhere on the board
MCU_EN: C12.1, SW1.1, SW4.1; also elsewhere on the board
START_N: R18.2, SW3.1; also elsewhere on the board
V3V3: R17.1, R18.1; also elsewhere on the board

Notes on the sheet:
02 USB reset / 2
M6-C1R1 candidate: REVIEW / ALL hardware measurements NOT RUN / no ordering or manufacture.

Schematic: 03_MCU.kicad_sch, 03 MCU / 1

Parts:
C20: 10u 10V; C_0603_1608Metric_CTL; MPN CL10A106KP8NNNC
C21: 100n; C_0603_1608Metric_CTL; MPN CL10B104KB8NNNC
J3: UART recovery / GND; UART_61300311121; MPN 61300311121; not fitted
U10: ESP32-S3-WROOM-1U-N4; ESP32_S3_WROOM_1U_N4_L2; MPN ESP32-S3-WROOM-1U-N4

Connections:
AF_PWM: U10.6 (6_GPIO6); also elsewhere on the board
ARM: U10.34 (34_GPIO41); also elsewhere on the board
BAT_ADC: U10.39 (39_GPIO1); also elsewhere on the board
BOOT: U10.27 (27_GPIO0); also elsewhere on the board
GND: C20.2, C21.2, J3.1 (1_IO), U10.1 (1_GND), U10.40 (40_GND), U10.41 (41_GND_EP); also elsewhere on the board
INIT_OK: U10.22 (22_GPIO14); also elsewhere on the board
KEY: U10.24 (24_GPIO47); also elsewhere on the board
LEVEL_PWM: U10.7 (7_GPIO7); also elsewhere on the board
LORA_BUSY: U10.8 (8_GPIO15); also elsewhere on the board
LORA_DIO1: U10.9 (9_GPIO16); also elsewhere on the board
LORA_NSS: U10.18 (18_GPIO10); also elsewhere on the board
LORA_RESET: U10.33 (33_GPIO40); also elsewhere on the board
MCU_EN: U10.3 (3_EN); also elsewhere on the board
MODULE_ID_ADC: U10.4 (4_GPIO4); also elsewhere on the board
MUTE_RELEASE: U10.35 (35_GPIO42); also elsewhere on the board
PACK_ID_ADC: U10.38 (38_GPIO2); also elsewhere on the board
PA_RAIL_ADC: U10.5 (5_GPIO5); also elsewhere on the board
PROGRESS: U10.32 (32_GPIO39); also elsewhere on the board
REC_RX: J3.3 (3_IO); also elsewhere on the board
REC_TX: J3.2 (2_IO); also elsewhere on the board
RF2M_FAULT: U10.23 (23_GPIO21); also elsewhere on the board
RF2M_SCL: U10.11 (11_GPIO18); also elsewhere on the board
RF2M_SDA: U10.10 (10_GPIO17); also elsewhere on the board
RF80_FAULT: U10.28 (28_GPIO35); also elsewhere on the board
RTC80_SCL: U10.17 (17_GPIO9); also elsewhere on the board
RTC80_SDA: U10.12 (12_GPIO8); also elsewhere on the board
SHIFT_LATCH: U10.31 (31_GPIO38); also elsewhere on the board
SLOT: U10.25 (25_GPIO48); also elsewhere on the board
SPI_MISO: U10.21 (21_GPIO13); also elsewhere on the board
SPI_MOSI: U10.19 (19_GPIO11); also elsewhere on the board
SPI_SCK: U10.20 (20_GPIO12); also elsewhere on the board
START_N: U10.29 (29_GPIO36); also elsewhere on the board
STRAP3: U10.15 (15_GPIO3); also elsewhere on the board
STRAP46: U10.16 (16_GPIO46); also elsewhere on the board
UART_RX: U10.36 (36_GPIO44); also elsewhere on the board
UART_TX: U10.37 (37_GPIO43); also elsewhere on the board
USB_DM: U10.13 (13_GPIO19); also elsewhere on the board
USB_DP: U10.14 (14_GPIO20); also elsewhere on the board
USB_VBUS_N: U10.30 (30_GPIO37); also elsewhere on the board
V3V3: C20.1, C21.1, U10.2 (2_3V3); also elsewhere on the board

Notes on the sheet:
03 MCU / 1
M6-C1R1 candidate: REVIEW / ALL hardware measurements NOT RUN / no ordering or manufacture.

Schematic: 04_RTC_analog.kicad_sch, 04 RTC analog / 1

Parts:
BT1: CR1220 primary; BatteryHolder_Keystone_3000_1x12mm_CTL; MPN 3000
C22, C23, C24, C25, C26, C27, C28: 100n; C_0603_1608Metric_CTL; MPN CL10B104KB8NNNC
D20: BAS116 no cell charging; SOT-23_CTL; MPN BAS116,115
R20: 1k; R_0603_1608Metric_CTL; MPN RC0603FR-071KL
R22, R23, R24, R25: 4.7k; R_0603_1608Metric_CTL; MPN RC0603FR-074K7L
R26: 33k; R_0603_1608Metric_CTL; MPN RC0603FR-0733KL
U20: RV-3032-C7 2.5ppm; RV3032_C7; MPN RV-3032-C7-32.768KHZ-2.5PPM-TA-QA
U21: TMUX1511PWR; TSSOP-14_4.4x5mm_P0.65mm_CTL; MPN TMUX1511PWR

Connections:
BACKUP_D: D20.3 (3_K), R20.1
BAT_ADC: U21.3 (3_IO); also elsewhere on the board
BAT_DIV: C24.1, U21.2 (2_IO); also elsewhere on the board
CELL_POS: BT1.1 (+), D20.1 (1_A)
GND: BT1.2 (-), C22.2, C23.2, C24.2, C25.2, C26.2, C27.2, C28.2, U20.4 (4_EVI), U20.5 (5_VSS), U21.7 (7_GND); also elsewhere on the board
MODULE_ID_ADC: U21.8 (8_IO); also elsewhere on the board
PACK_ID_ADC: U21.6 (6_IO); also elsewhere on the board
PACK_ID_SAFE: C25.1, U21.5 (5_IO); also elsewhere on the board
PA_RAIL_ADC: U21.11 (11_IO); also elsewhere on the board
RF2M_MODULE_ID: C26.1, R26.2, U21.9 (9_IO); also elsewhere on the board
RF2M_PA_RAIL_ADC: C27.1, U21.12 (12_IO); also elsewhere on the board
RF2M_SCL: R25.2; also elsewhere on the board
RF2M_SDA: R24.2; also elsewhere on the board
RTC80_SCL: R23.2, U20.8 (8_SCL); also elsewhere on the board
RTC80_SDA: R22.2, U20.2 (2_SDA); also elsewhere on the board
RTC_BACKUP: C22.1, R20.2, U20.1 (1_VBACKUP)
V3V3: C23.1, C28.1, R22.1, R23.1, R24.1, R25.1, R26.1, U20.6 (6_VDD), U21.1 (1_IO), U21.4 (4_IO), U21.10 (10_IO), U21.13 (13_IO), U21.14 (14_VDD); also elsewhere on the board

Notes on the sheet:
04 RTC analog / 1
M6-C1R1 candidate: REVIEW / ALL hardware measurements NOT RUN / no ordering or manufacture.

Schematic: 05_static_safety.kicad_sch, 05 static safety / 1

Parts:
C30, C31: 100n; C_0603_1608Metric_CTL; MPN CL10B104KB8NNNC
R30, R31, R32, R33, R34, R35, R36, R37, R38, R39, R40, R41, R42, R43: 10k; R_0603_1608Metric_CTL; MPN RC0603FR-0710KL
U30, U31: SN74HC595PWR; TSSOP-16_4.4x5mm_P0.65mm_CTL; MPN SN74HC595PWR

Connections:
BAND2: U31.7 (7_Q); also elsewhere on the board
BUS2M: R42.1, U31.4 (4_Q); also elsewhere on the board
BUS80: R41.1, U31.3 (3_Q); also elsewhere on the board
FOX_REQ: R31.1, U30.1 (1_Q); also elsewhere on the board
GND: C30.2, C31.2, R30.2, R31.2, R32.2, R33.2, R34.2, R35.2, R36.2, R37.2, R38.2, R39.2, R40.2, R41.2, R42.2, R43.2, U30.8 (8_GND), U31.8 (8_GND); also elsewhere on the board
LED_ARM: R43.1, U31.5 (5_Q); also elsewhere on the board
LED_FAULT: U31.6 (6_Q); also elsewhere on the board
MCU_EN: U30.10 (10_SRCLR_N), U31.10 (10_SRCLR_N); also elsewhere on the board
PACK4_SOFT: R34.1, U30.4 (4_Q); also elsewhere on the board
PATH_TRAIN: R35.1, U30.5 (5_Q); also elsewhere on the board
PA_PREPARE: R38.1, U31.15 (15_Q); also elsewhere on the board
PA_REQ: R30.1, U30.15 (15_Q); also elsewhere on the board
POWER2M: R40.1, U31.2 (2_Q); also elsewhere on the board
POWER80: R39.1, U31.1 (1_Q); also elsewhere on the board
PREPARE: R37.1, U30.7 (7_Q); also elsewhere on the board
PROFILE_FULL: R36.1, U30.6 (6_Q); also elsewhere on the board
PWR0: R32.1, U30.2 (2_Q); also elsewhere on the board
PWR1: R33.1, U30.3 (3_Q); also elsewhere on the board
SAFE_OE_N: U30.13 (13_OE_N), U31.13 (13_OE_N); also elsewhere on the board
SHIFT_CHAIN: U30.9 (9_QH_S), U31.14 (14_SER)
SHIFT_LATCH: U30.12 (12_RCLK), U31.12 (12_RCLK); also elsewhere on the board
SPI_MOSI: U30.14 (14_SER); also elsewhere on the board
SPI_SCK: U30.11 (11_SRCLK), U31.11 (11_SRCLK); also elsewhere on the board
V3V3: C30.1, C31.1, U30.16 (16_VCC), U31.16 (16_VCC); also elsewhere on the board

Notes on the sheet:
05 static safety / 1
M6-C1R1 candidate: REVIEW / ALL hardware measurements NOT RUN / no ordering or manufacture.

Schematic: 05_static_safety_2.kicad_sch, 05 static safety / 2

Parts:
R44, R45, R50, R51, R52, R53, R54, R55, R56, R57, R58, R59: 10k; R_0603_1608Metric_CTL; MPN RC0603FR-0710KL
U32, U36: SN74LVC1G04DBVR; SOT-23-5_CTL; MPN SN74LVC1G04DBVR
U33: SN74LVC1G10DBVR; SOT-23-6_CTL; MPN SN74LVC1G10DBVR
U34: SN74LVC2G04DCKR; SOT-363_SC-70-6_CTL; MPN SN74LVC2G04DCKR
U35: SN74LVC00APWR; TSSOP-14_4.4x5mm_P0.65mm_CTL; MPN SN74LVC00APWR
U37: SN74LVC08APWR; TSSOP-14_4.4x5mm_P0.65mm_CTL; MPN SN74LVC08APWR

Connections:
AF_PWM: R56.1; also elsewhere on the board
ARM: R51.1, U36.2 (2_A); also elsewhere on the board
BAND2: R45.1, U34.4 (4_2A), U35.5 (5_2B); also elsewhere on the board
BAND80: U34.2 (2_2Y), U35.2 (2_1B)
BUS2M: U37.4 (4_2A); also elsewhere on the board
BUS2M_EN: U37.6 (6_2Y); also elsewhere on the board
BUS80: U37.1 (1_1A); also elsewhere on the board
BUS80_EN: U37.3 (3_1Y); also elsewhere on the board
DISARMED: U36.4 (4_Y), U37.2 (2_1B), U37.5 (5_2B)
GND: R44.2, R45.2, R50.2, R51.2, R52.2, R53.2, R54.2, R55.2, R56.2, R57.2, R58.2, U32.3 (3_GND), U33.3 (3_GND), U34.3 (3_GND), U35.7 (7_GND), U35.9 (9_3A), U35.10 (10_3B), U35.12 (12_4A), U35.13 (13_4B), U36.3 (3_GND), U37.7 (7_GND), U37.9 (9_3A), U37.10 (10_3B), U37.12 (12_4A), U37.13 (13_4B); also elsewhere on the board
INIT_OK: R50.1, U33.1 (1_A); also elsewhere on the board
KEY: R54.1; also elsewhere on the board
LED_FAULT: R44.1; also elsewhere on the board
LEVEL_PWM: R57.1; also elsewhere on the board
MCU_EN: U33.2 (2_B); also elsewhere on the board
MUTE_RELEASE: R52.1; also elsewhere on the board
OE2M_N: U35.6 (6_2Y); also elsewhere on the board
OE80_N: U35.3 (3_1Y); also elsewhere on the board
PACK_ABSENT: U32.2 (2_A); also elsewhere on the board
PACK_PRESENT: U32.4 (4_Y), U33.6 (6_C)
PROGRESS: R53.1; also elsewhere on the board
SAFE: U34.5 (5_1Y), U35.1 (1_1A), U35.4 (4_2A); also elsewhere on the board
SAFE_OE_N: R59.2, U33.4 (4_Y), U34.1 (1_1A); also elsewhere on the board
SHIFT_LATCH: R58.1; also elsewhere on the board
SLOT: R55.1; also elsewhere on the board
V3V3: R59.1, U32.5 (5_VCC), U33.5 (5_VCC), U34.6 (6_VCC), U35.14 (14_VCC), U36.5 (5_VCC), U37.14 (14_VCC); also elsewhere on the board

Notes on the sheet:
05 static safety / 2
M6-C1R1 candidate: REVIEW / ALL hardware measurements NOT RUN / no ordering or manufacture.

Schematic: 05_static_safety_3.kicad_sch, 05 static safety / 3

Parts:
C32, C33, C34, C35, C36, C37: 100n; C_0603_1608Metric_CTL; MPN CL10B104KB8NNNC
D30, D32: status; LED_0603_1608Metric_CTL; MPN LTST-C190KGKT
D31: status; LED_0603_1608Metric_CTL; MPN LTST-C190KRKT
R60, R61, R62: 2.2k; R_0603_1608Metric_CTL; MPN RC0603FR-072K2L

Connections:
D30_A: D30.2 (A), R60.2
D31_A: D31.2 (A), R61.2
D32_A: D32.2 (A), R62.2
GND: C32.2, C33.2, C34.2, C35.2, C36.2, C37.2, D30.1 (K), D31.1 (K), D32.1 (K); also elsewhere on the board
LED_ARM: R60.1; also elsewhere on the board
LED_FAULT: R61.1; also elsewhere on the board
V3V3: C32.1, C33.1, C34.1, C35.1, C36.1, C37.1, R62.1; also elsewhere on the board

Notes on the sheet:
05 static safety / 3
M6-C1R1 candidate: REVIEW / ALL hardware measurements NOT RUN / no ordering or manufacture.
